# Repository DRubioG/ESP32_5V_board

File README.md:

# ESP32_5V
 This board updates the voltage of an ESP32

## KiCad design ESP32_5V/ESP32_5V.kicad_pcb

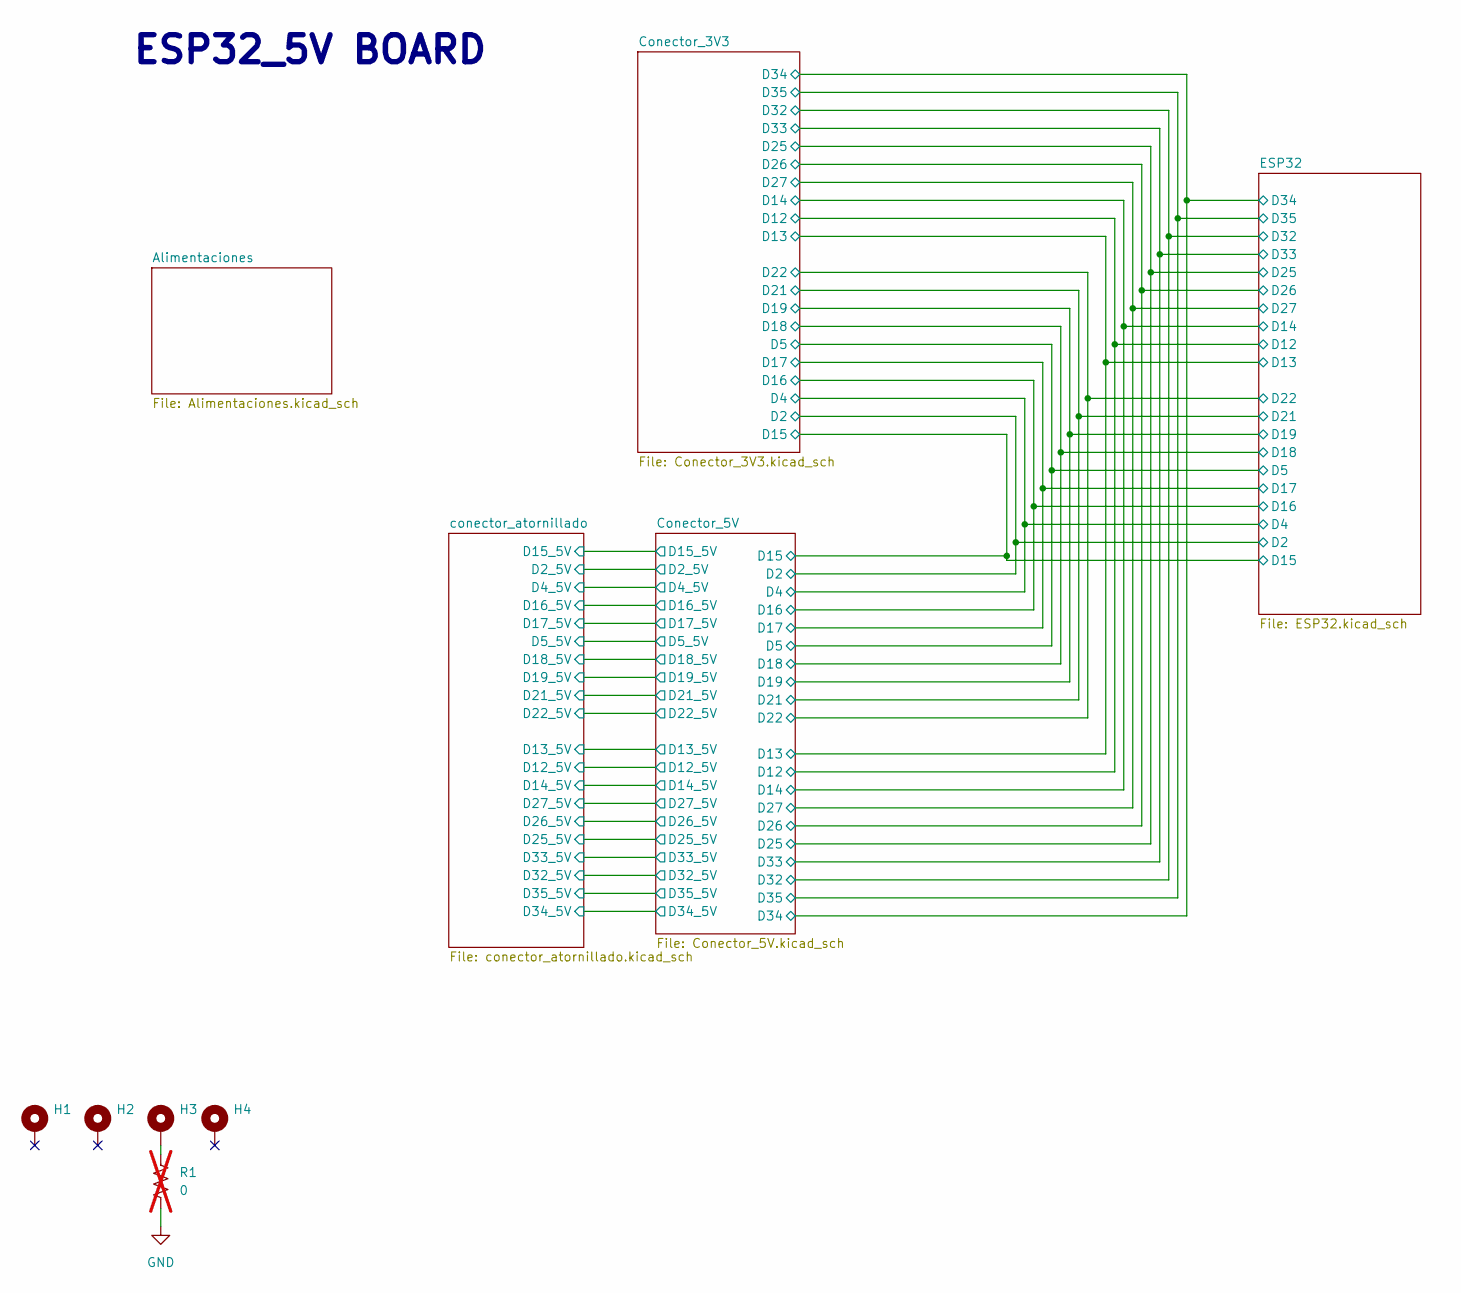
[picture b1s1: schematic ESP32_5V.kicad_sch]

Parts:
H1, H2, H3, H4: MountingHole_Pad; MountingHole_3.2mm_M3_Pad_Via
R1: 0; R_0805_2012Metric_Pad1.20x1.40mm_HandSolder; not fitted

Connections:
GND: R1.2; also elsewhere on the board
unnamed: H3.1 (1_1), R1.1

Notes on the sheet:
ESP32_5V BOARD

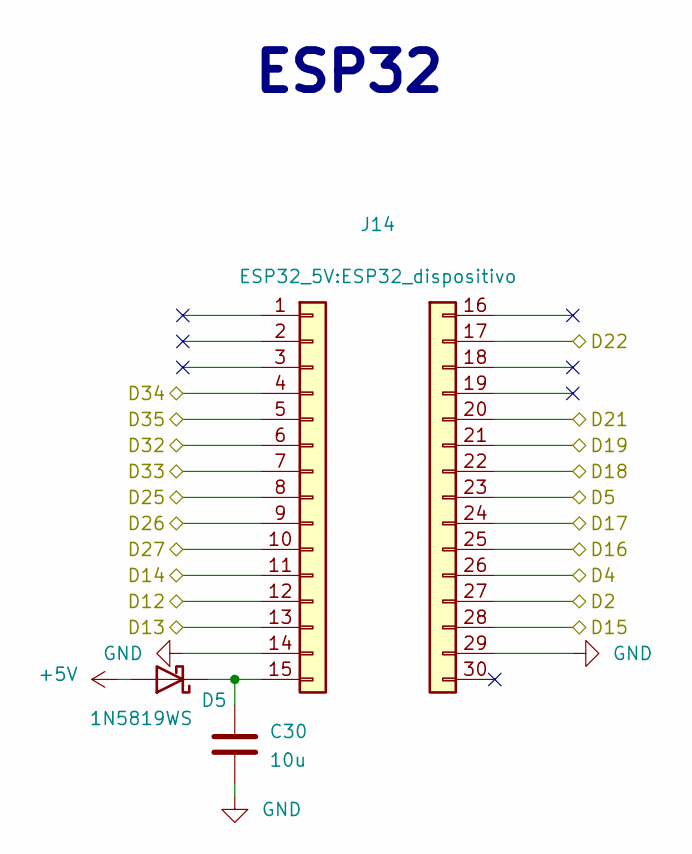
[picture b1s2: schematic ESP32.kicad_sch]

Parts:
C30: 10u; C_1206_3216Metric
D5: 1N5819WS; D_SOD-323
J14: ESP32_dispositivo

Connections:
+5V: D5.2 (A); also elsewhere on the board
/Conector_3V3/D2: J14.27; also elsewhere on the board
/Conector_3V3/D4: J14.26; also elsewhere on the board
/Conector_3V3/D5: J14.23; also elsewhere on the board
/Conector_3V3/D12: J14.12; also elsewhere on the board
/Conector_3V3/D13: J14.13; also elsewhere on the board
/Conector_3V3/D14: J14.11; also elsewhere on the board
/Conector_3V3/D15: J14.28; also elsewhere on the board
/Conector_3V3/D16: J14.25; also elsewhere on the board
/Conector_3V3/D17: J14.24; also elsewhere on the board
/Conector_3V3/D18: J14.22; also elsewhere on the board
/Conector_3V3/D19: J14.21; also elsewhere on the board
/Conector_3V3/D21: J14.20; also elsewhere on the board
/Conector_3V3/D22: J14.17; also elsewhere on the board
/Conector_3V3/D25: J14.8; also elsewhere on the board
/Conector_3V3/D26: J14.9; also elsewhere on the board
/Conector_3V3/D27: J14.10; also elsewhere on the board
/Conector_3V3/D32: J14.6; also elsewhere on the board
/Conector_3V3/D33: J14.7; also elsewhere on the board
/Conector_3V3/D34: J14.4; also elsewhere on the board
/Conector_3V3/D35: J14.5; also elsewhere on the board
GND: C30.2, J14.14, J14.29; also elsewhere on the board
unnamed: C30.1, D5.1 (K), J14.15

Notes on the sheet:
ESP32

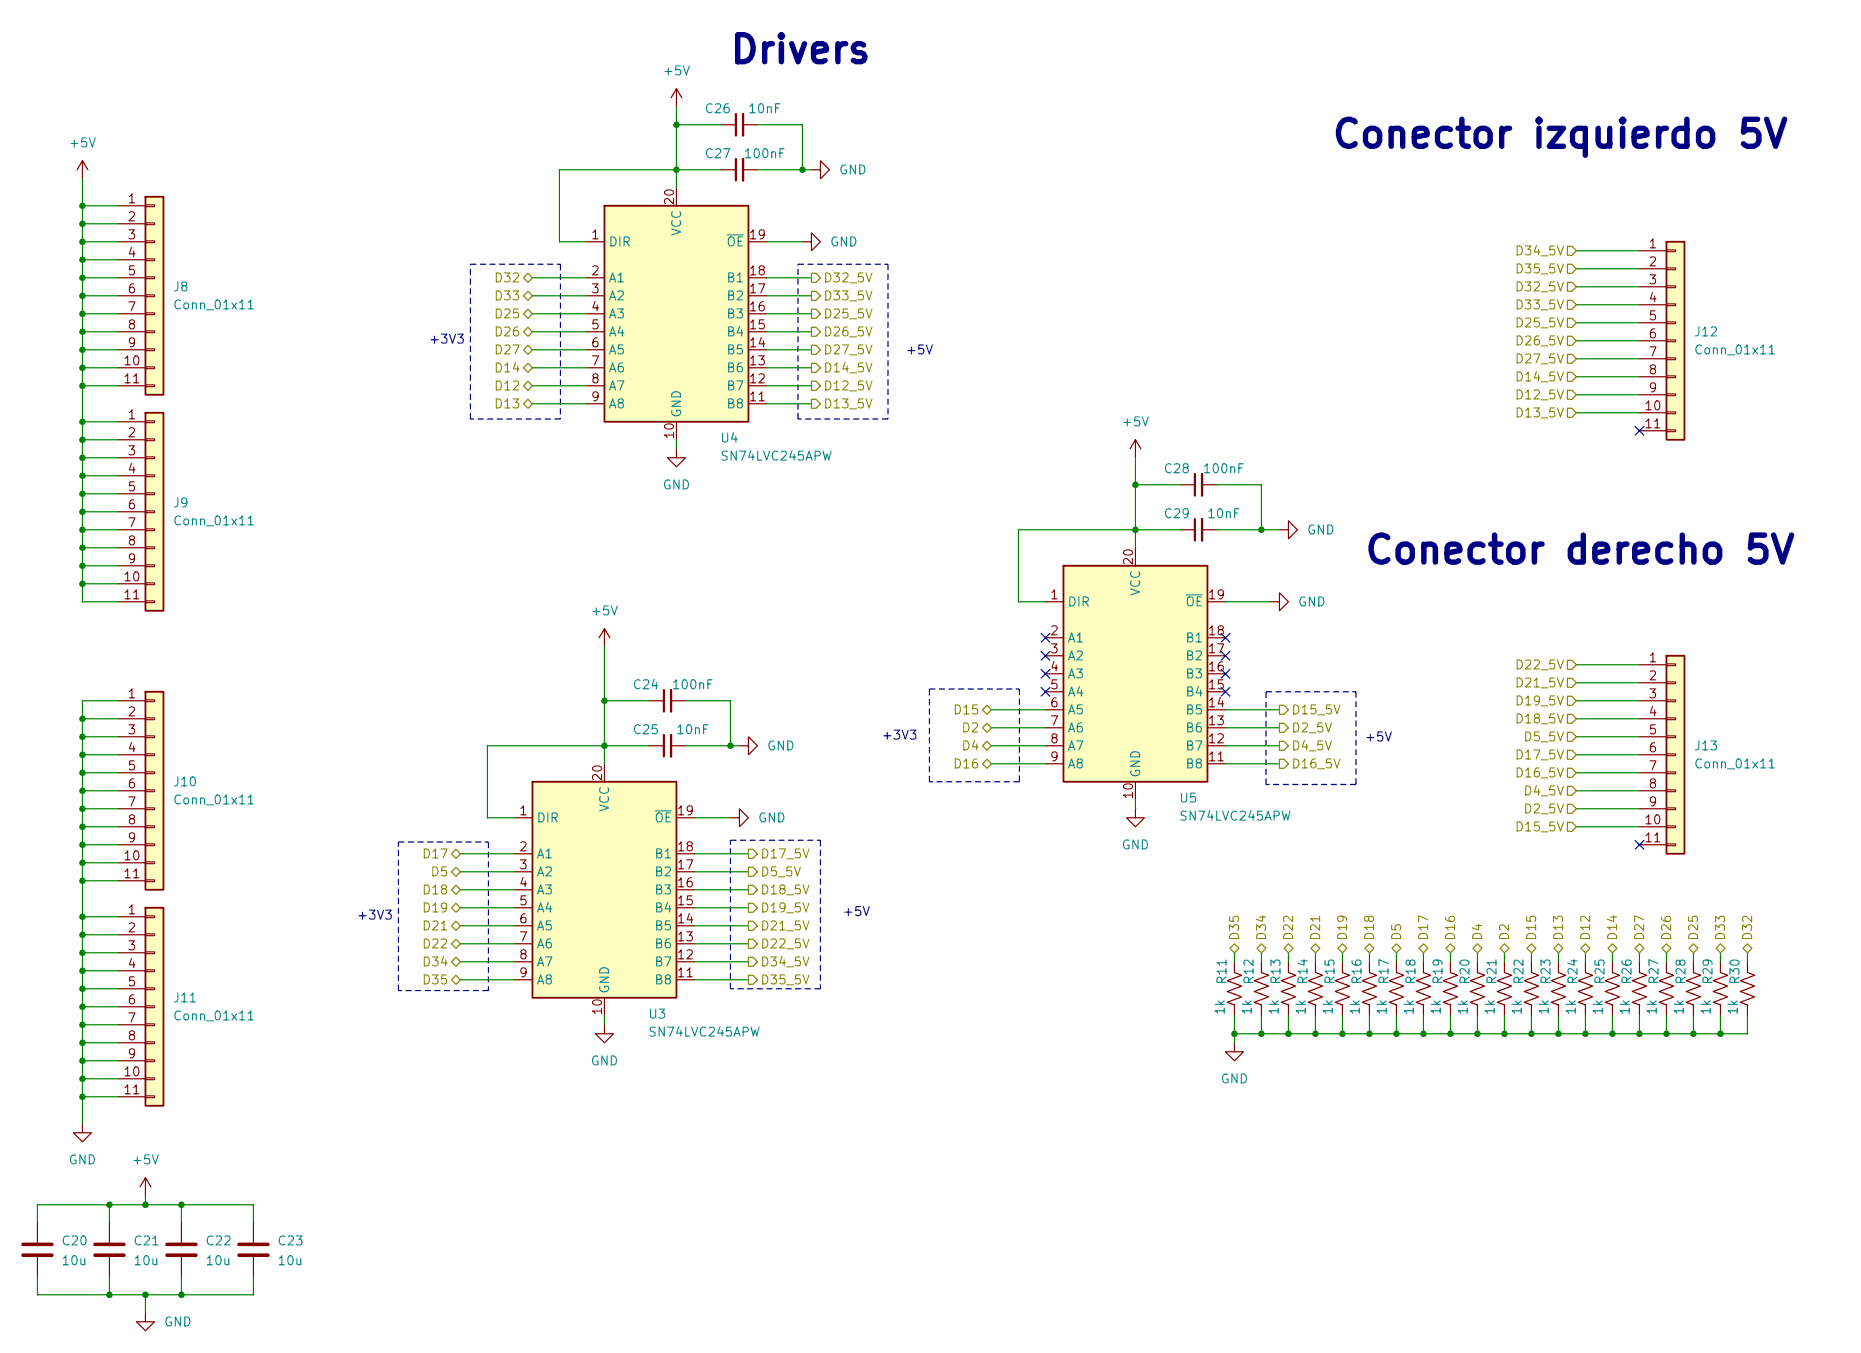
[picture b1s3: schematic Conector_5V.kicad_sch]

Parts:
C20, C21, C22, C23: 10u; C_1206_3216Metric
C24, C27, C28: 100nF; C_0805_2012Metric_Pad1.18x1.45mm_HandSolder
C25, C26, C29: 10nF; C_0805_2012Metric_Pad1.18x1.45mm_HandSolder
J8, J9, J10, J11, J12, J13: Conn_01x11; PinHeader_1x11_P2.54mm_Vertical
R11, R12, R13, R14, R15, R16, R17, R18, R19, R20, R21, R22, R23, R24, R25, R26, R27, R28, R29, R30: 1k; R_0805_2012Metric_Pad1.20x1.40mm_HandSolder
U3, U4, U5: SN74LVC245APW; TSSOP-20_4.4x6.5mm_P0.65mm

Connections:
+5V: C20.1, C21.1, C22.1, C23.1, C24.1, C25.1, C26.1, C27.1, C28.1, C29.1, J8.1, J8.2, J8.3, J8.4, J8.5, J8.6, J8.7, J8.8, J8.9, J8.10, J8.11, J9.1, J9.2, J9.3, J9.4, J9.5, J9.6, J9.7, J9.8, J9.9, J9.10, J9.11, U3.1 (DIR), U3.20 (VCC), U4.1 (DIR), U4.20 (VCC), U5.1 (DIR), U5.20 (VCC); also elsewhere on the board
/Conector_3V3/D2: R21.1, U5.7 (A6); also elsewhere on the board
/Conector_3V3/D4: R20.1, U5.8 (A7); also elsewhere on the board
/Conector_3V3/D5: R17.1, U3.3 (A2); also elsewhere on the board
/Conector_3V3/D12: R24.1, U4.8 (A7); also elsewhere on the board
/Conector_3V3/D13: R23.1, U4.9 (A8); also elsewhere on the board
/Conector_3V3/D14: R25.1, U4.7 (A6); also elsewhere on the board
/Conector_3V3/D15: R22.1, U5.6 (A5); also elsewhere on the board
/Conector_3V3/D16: R19.1, U5.9 (A8); also elsewhere on the board
/Conector_3V3/D17: R18.1, U3.2 (A1); also elsewhere on the board
/Conector_3V3/D18: R16.1, U3.4 (A3); also elsewhere on the board
/Conector_3V3/D19: R15.1, U3.5 (A4); also elsewhere on the board
/Conector_3V3/D21: R14.1, U3.6 (A5); also elsewhere on the board
/Conector_3V3/D22: R13.1, U3.7 (A6); also elsewhere on the board
/Conector_3V3/D25: R28.1, U4.4 (A3); also elsewhere on the board
/Conector_3V3/D26: R27.1, U4.5 (A4); also elsewhere on the board
/Conector_3V3/D27: R26.1, U4.6 (A5); also elsewhere on the board
/Conector_3V3/D32: R30.1, U4.2 (A1); also elsewhere on the board
/Conector_3V3/D33: R29.1, U4.3 (A2); also elsewhere on the board
/Conector_3V3/D34: R12.1, U3.8 (A7); also elsewhere on the board
/Conector_3V3/D35: R11.1, U3.9 (A8); also elsewhere on the board
/Conector_5V/D2_5V: J13.9, U5.13 (B6); also elsewhere on the board
/Conector_5V/D4_5V: J13.8, U5.12 (B7); also elsewhere on the board
/Conector_5V/D5_5V: J13.5, U3.17 (B2); also elsewhere on the board
/Conector_5V/D12_5V: J12.9, U4.12 (B7); also elsewhere on the board
/Conector_5V/D13_5V: J12.10, U4.11 (B8); also elsewhere on the board
/Conector_5V/D14_5V: J12.8, U4.13 (B6); also elsewhere on the board
/Conector_5V/D15_5V: J13.10, U5.14 (B5); also elsewhere on the board
/Conector_5V/D16_5V: J13.7, U5.11 (B8); also elsewhere on the board
/Conector_5V/D17_5V: J13.6, U3.18 (B1); also elsewhere on the board
/Conector_5V/D18_5V: J13.4, U3.16 (B3); also elsewhere on the board
/Conector_5V/D19_5V: J13.3, U3.15 (B4); also elsewhere on the board
/Conector_5V/D21_5V: J13.2, U3.14 (B5); also elsewhere on the board
/Conector_5V/D22_5V: J13.1, U3.13 (B6); also elsewhere on the board
/Conector_5V/D25_5V: J12.5, U4.16 (B3); also elsewhere on the board
/Conector_5V/D26_5V: J12.6, U4.15 (B4); also elsewhere on the board
/Conector_5V/D27_5V: J12.7, U4.14 (B5); also elsewhere on the board
/Conector_5V/D32_5V: J12.3, U4.18 (B1); also elsewhere on the board
/Conector_5V/D33_5V: J12.4, U4.17 (B2); also elsewhere on the board
/Conector_5V/D34_5V: J12.1, U3.12 (B7); also elsewhere on the board
/Conector_5V/D35_5V: J12.2, U3.11 (B8); also elsewhere on the board
GND: C20.2, C21.2, C22.2, C23.2, C24.2, C25.2, C26.2, C27.2, C28.2, C29.2, J10.1, J10.2, J10.3, J10.4, J10.5, J10.6, J10.7, J10.8, J10.9, J10.10, J10.11, J11.1, J11.2, J11.3, J11.4, J11.5, J11.6, J11.7, J11.8, J11.9, J11.10, J11.11, R11.2, R12.2, R13.2, R14.2, R15.2, R16.2, R17.2, R18.2, R19.2, R20.2, R21.2, R22.2, R23.2, R24.2, R25.2, R26.2, R27.2, R28.2, R29.2, R30.2, U3.10 (GND), U3.19 (~OE), U4.10 (GND), U4.19 (~OE), U5.10 (GND), U5.19 (~OE); also elsewhere on the board

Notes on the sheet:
Conector izquierdo 5V
+5V
+3V3
Conector derecho 5V
Drivers

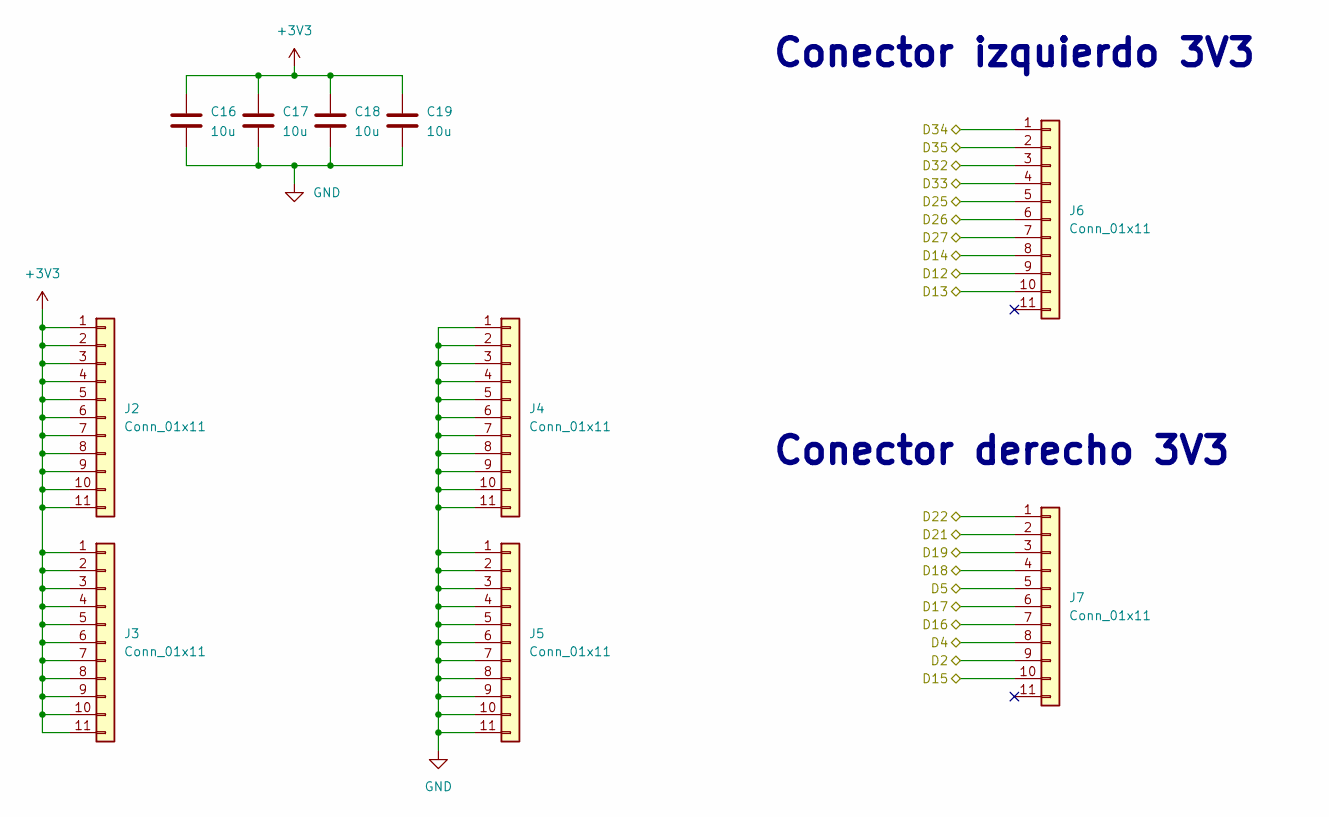
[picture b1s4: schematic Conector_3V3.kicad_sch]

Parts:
C16, C17, C18, C19: 10u; C_1206_3216Metric
J2, J3, J4, J5, J6, J7: Conn_01x11; PinHeader_1x11_P2.54mm_Vertical

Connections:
+3V3: C16.1, C17.1, C18.1, C19.1, J2.1, J2.2, J2.3, J2.4, J2.5, J2.6, J2.7, J2.8, J2.9, J2.10, J2.11, J3.1, J3.2, J3.3, J3.4, J3.5, J3.6, J3.7, J3.8, J3.9, J3.10, J3.11; also elsewhere on the board
/Conector_3V3/D2: J7.9; also elsewhere on the board
/Conector_3V3/D4: J7.8; also elsewhere on the board
/Conector_3V3/D5: J7.5; also elsewhere on the board
/Conector_3V3/D12: J6.9; also elsewhere on the board
/Conector_3V3/D13: J6.10; also elsewhere on the board
/Conector_3V3/D14: J6.8; also elsewhere on the board
/Conector_3V3/D15: J7.10; also elsewhere on the board
/Conector_3V3/D16: J7.7; also elsewhere on the board
/Conector_3V3/D17: J7.6; also elsewhere on the board
/Conector_3V3/D18: J7.4; also elsewhere on the board
/Conector_3V3/D19: J7.3; also elsewhere on the board
/Conector_3V3/D21: J7.2; also elsewhere on the board
/Conector_3V3/D22: J7.1; also elsewhere on the board
/Conector_3V3/D25: J6.5; also elsewhere on the board
/Conector_3V3/D26: J6.6; also elsewhere on the board
/Conector_3V3/D27: J6.7; also elsewhere on the board
/Conector_3V3/D32: J6.3; also elsewhere on the board
/Conector_3V3/D33: J6.4; also elsewhere on the board
/Conector_3V3/D34: J6.1; also elsewhere on the board
/Conector_3V3/D35: J6.2; also elsewhere on the board
GND: C16.2, C17.2, C18.2, C19.2, J4.1, J4.2, J4.3, J4.4, J4.5, J4.6, J4.7, J4.8, J4.9, J4.10, J4.11, J5.1, J5.2, J5.3, J5.4, J5.5, J5.6, J5.7, J5.8, J5.9, J5.10, J5.11; also elsewhere on the board

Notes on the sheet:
Conector derecho 3V3
Conector izquierdo 3V3

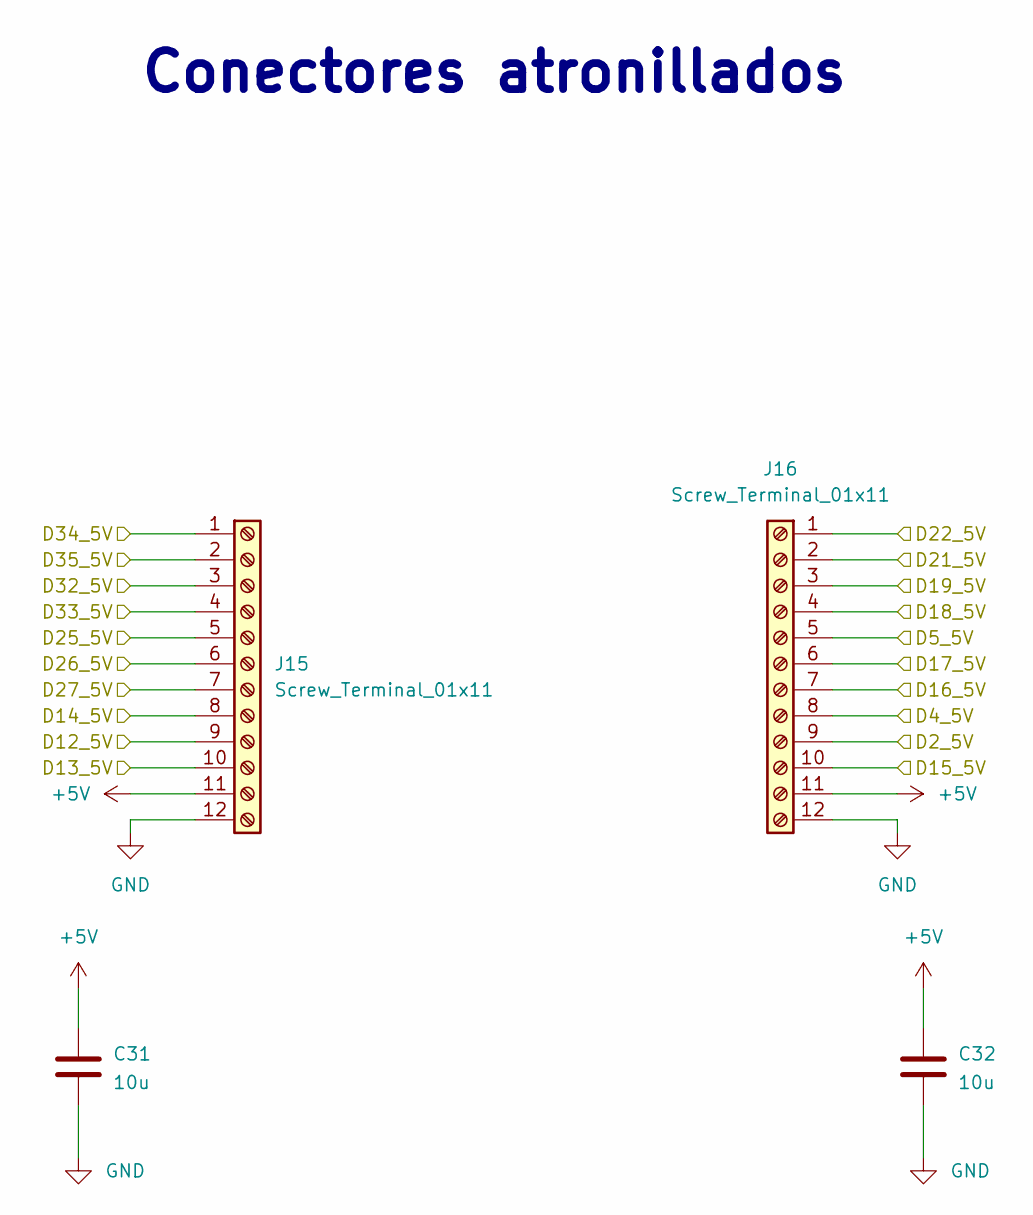
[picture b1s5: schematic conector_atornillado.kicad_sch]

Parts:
C31, C32: 10u; C_1206_3216Metric
J15, J16: Screw_Terminal_01x11; PinHeader_1x12_P2.54mm_Vertical

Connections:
+5V: C31.1, C32.1, J15.11, J16.11; also elsewhere on the board
/Conector_5V/D2_5V: J16.9; also elsewhere on the board
/Conector_5V/D4_5V: J16.8; also elsewhere on the board
/Conector_5V/D5_5V: J16.5; also elsewhere on the board
/Conector_5V/D12_5V: J15.9; also elsewhere on the board
/Conector_5V/D13_5V: J15.10; also elsewhere on the board
/Conector_5V/D14_5V: J15.8; also elsewhere on the board
/Conector_5V/D15_5V: J16.10; also elsewhere on the board
/Conector_5V/D16_5V: J16.7; also elsewhere on the board
/Conector_5V/D17_5V: J16.6; also elsewhere on the board
/Conector_5V/D18_5V: J16.4; also elsewhere on the board
/Conector_5V/D19_5V: J16.3; also elsewhere on the board
/Conector_5V/D21_5V: J16.2; also elsewhere on the board
/Conector_5V/D22_5V: J16.1; also elsewhere on the board
/Conector_5V/D25_5V: J15.5; also elsewhere on the board
/Conector_5V/D26_5V: J15.6; also elsewhere on the board
/Conector_5V/D27_5V: J15.7; also elsewhere on the board
/Conector_5V/D32_5V: J15.3; also elsewhere on the board
/Conector_5V/D33_5V: J15.4; also elsewhere on the board
/Conector_5V/D34_5V: J15.1; also elsewhere on the board
/Conector_5V/D35_5V: J15.2; also elsewhere on the board
GND: C31.2, C32.2, J15.12, J16.12; also elsewhere on the board

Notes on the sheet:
Conectores atronillados

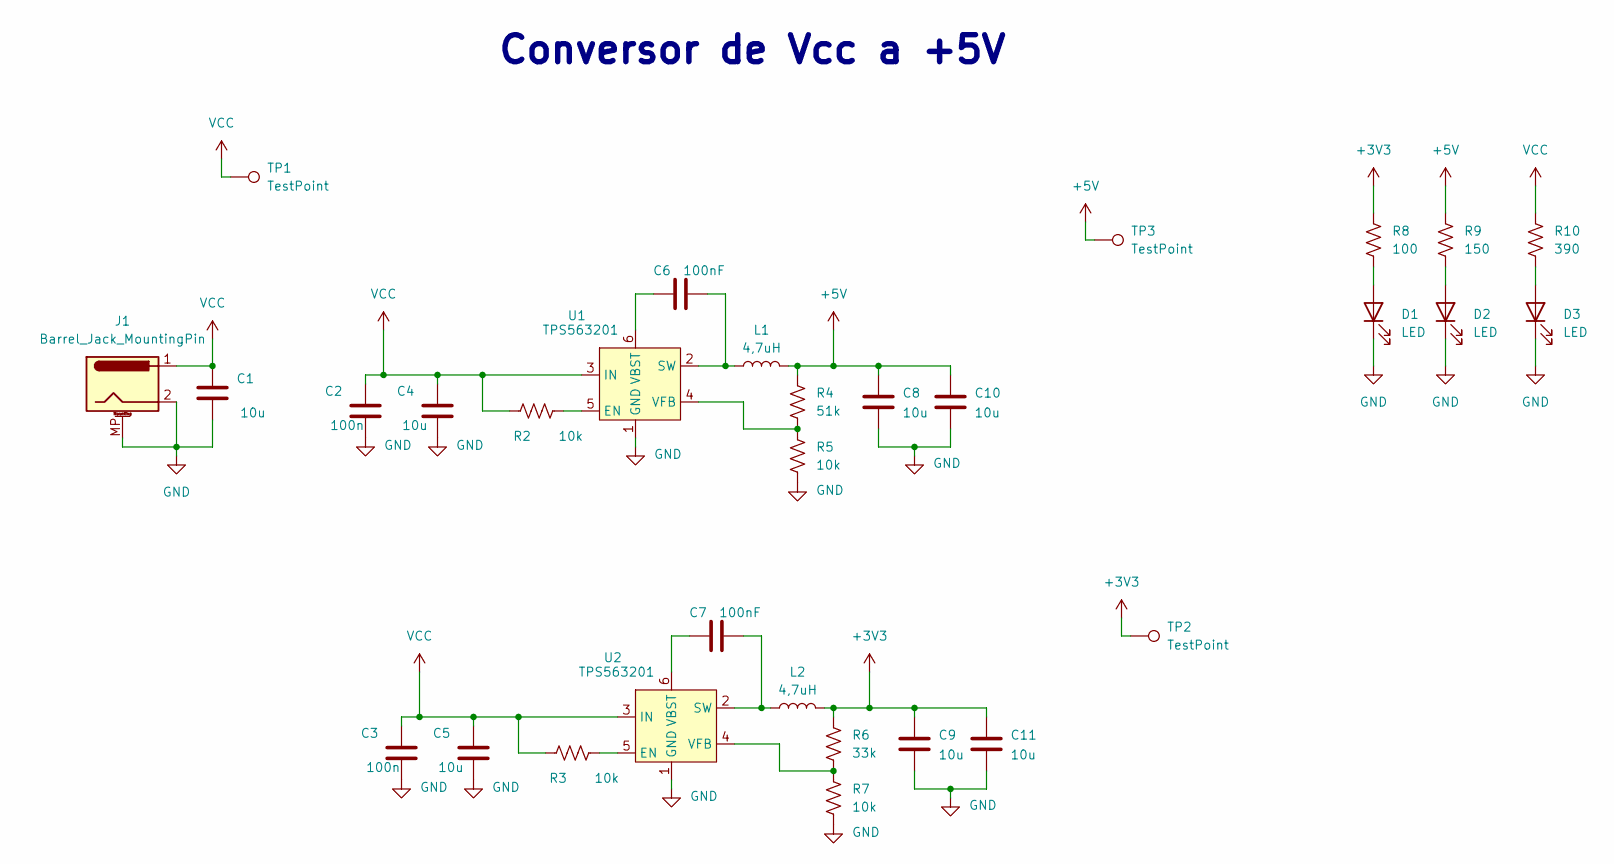
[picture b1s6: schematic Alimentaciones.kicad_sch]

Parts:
C1, C4, C5: 10u; C_1210_3225Metric
C2, C3: 100n; C_0805_2012Metric_Pad1.18x1.45mm_HandSolder
C6, C7: 100nF; C_0805_2012Metric_Pad1.18x1.45mm_HandSolder
C8, C9, C10, C11: 10u; C_1206_3216Metric
D1, D2, D3: LED; LED_0805_2012Metric_Pad1.15x1.40mm_HandSolder
J1: Barrel_Jack_MountingPin; BarrelJack_GCT_DCJ200-10-A_Horizontal
L1, L2: 4,7uH; L_6.3x6.3_H3
R2, R3, R5, R7: 10k; R_0805_2012Metric_Pad1.20x1.40mm_HandSolder
R4: 51k; R_0805_2012Metric_Pad1.20x1.40mm_HandSolder
R6: 33k; R_0805_2012Metric_Pad1.20x1.40mm_HandSolder
R8: 100; R_0805_2012Metric_Pad1.20x1.40mm_HandSolder
R9: 150; R_0805_2012Metric_Pad1.20x1.40mm_HandSolder
R10: 390; R_0805_2012Metric_Pad1.20x1.40mm_HandSolder
TP1, TP2, TP3: TestPoint; TestPoint_Pad_D2.0mm
U1, U2: TPS563201; SOT-23-6

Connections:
+3V3: C9.1, C11.1, L2.2, R6.1, R8.1, TP2.1 (1_1); also elsewhere on the board
+5V: C8.1, C10.1, L1.2, R4.1, R9.1, TP3.1 (1_1); also elsewhere on the board
GND: C1.2, C2.2, C3.2, C4.2, C5.2, C8.2, C9.2, C10.2, C11.2, D1.1 (K), D2.1 (K), D3.1 (K), J1.2, J1.MP (MountPin), R5.2, R7.2, U1.1 (GND), U2.1 (GND); also elsewhere on the board
unnamed: D1.2 (A), R8.2
unnamed: D2.2 (A), R9.2
unnamed: D3.2 (A), R10.2
unnamed: R2.1, U1.5 (EN)
unnamed: C6.2, L1.1, U1.2 (SW)
unnamed: C6.1, U1.6 (VBST)
unnamed: R4.2, R5.1, U1.4 (VFB)
unnamed: R3.1, U2.5 (EN)
unnamed: C7.2, L2.1, U2.2 (SW)
unnamed: C7.1, U2.6 (VBST)
unnamed: R6.2, R7.1, U2.4 (VFB)
VCC: C1.1, C2.1, C3.1, C4.1, C5.1, J1.1, R2.2, R3.2, R10.1, TP1.1 (1_1), U1.3 (IN), U2.3 (IN)

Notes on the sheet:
Conversor de Vcc a +5V

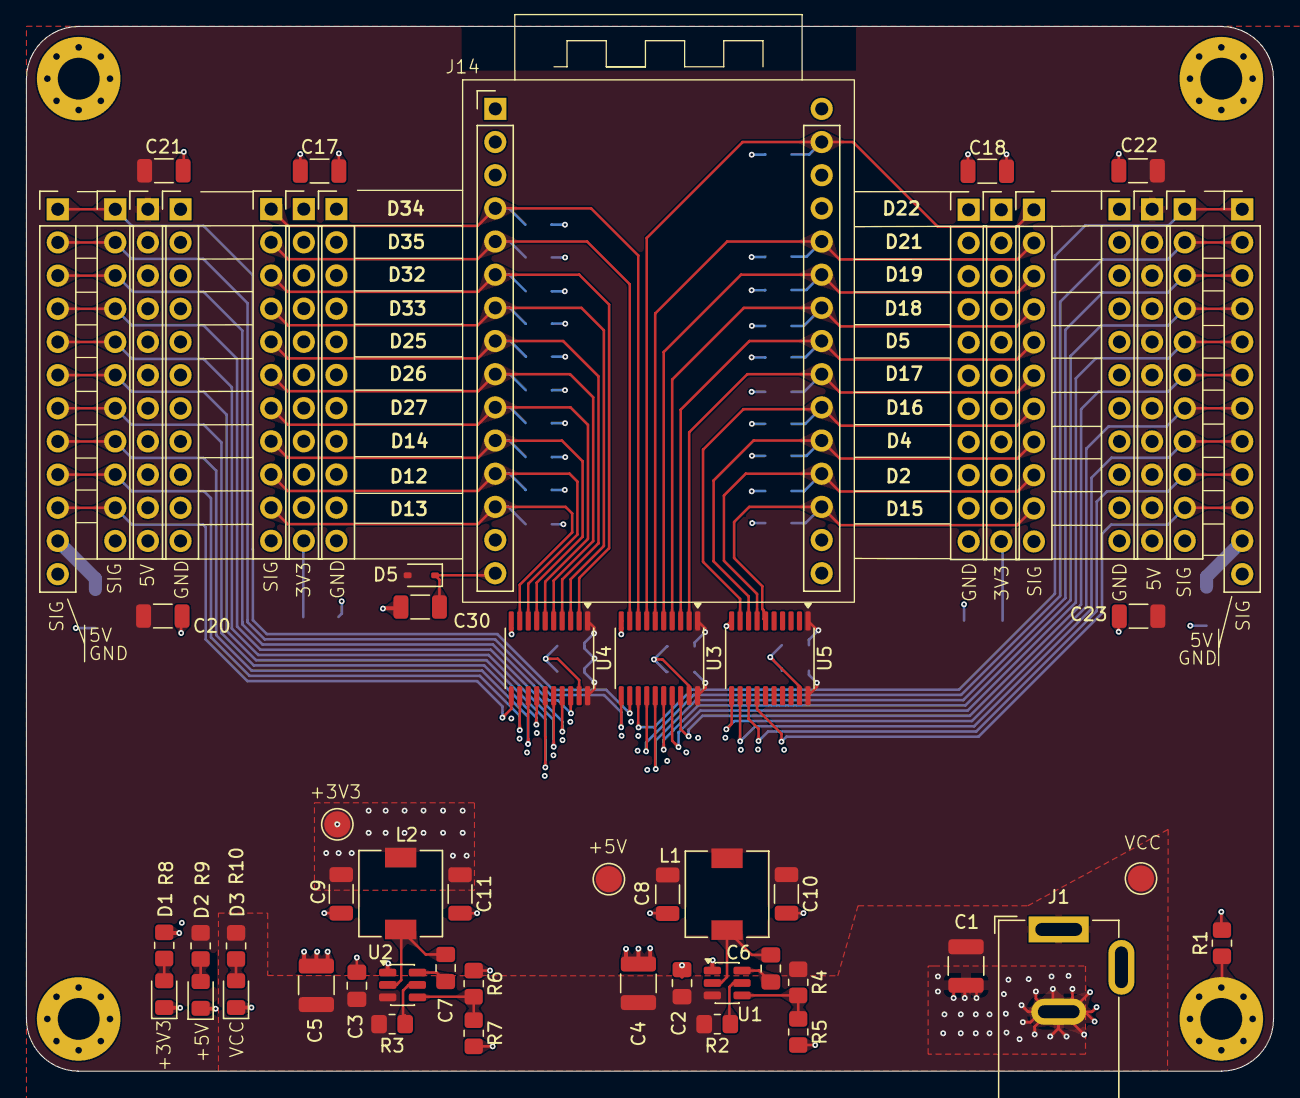
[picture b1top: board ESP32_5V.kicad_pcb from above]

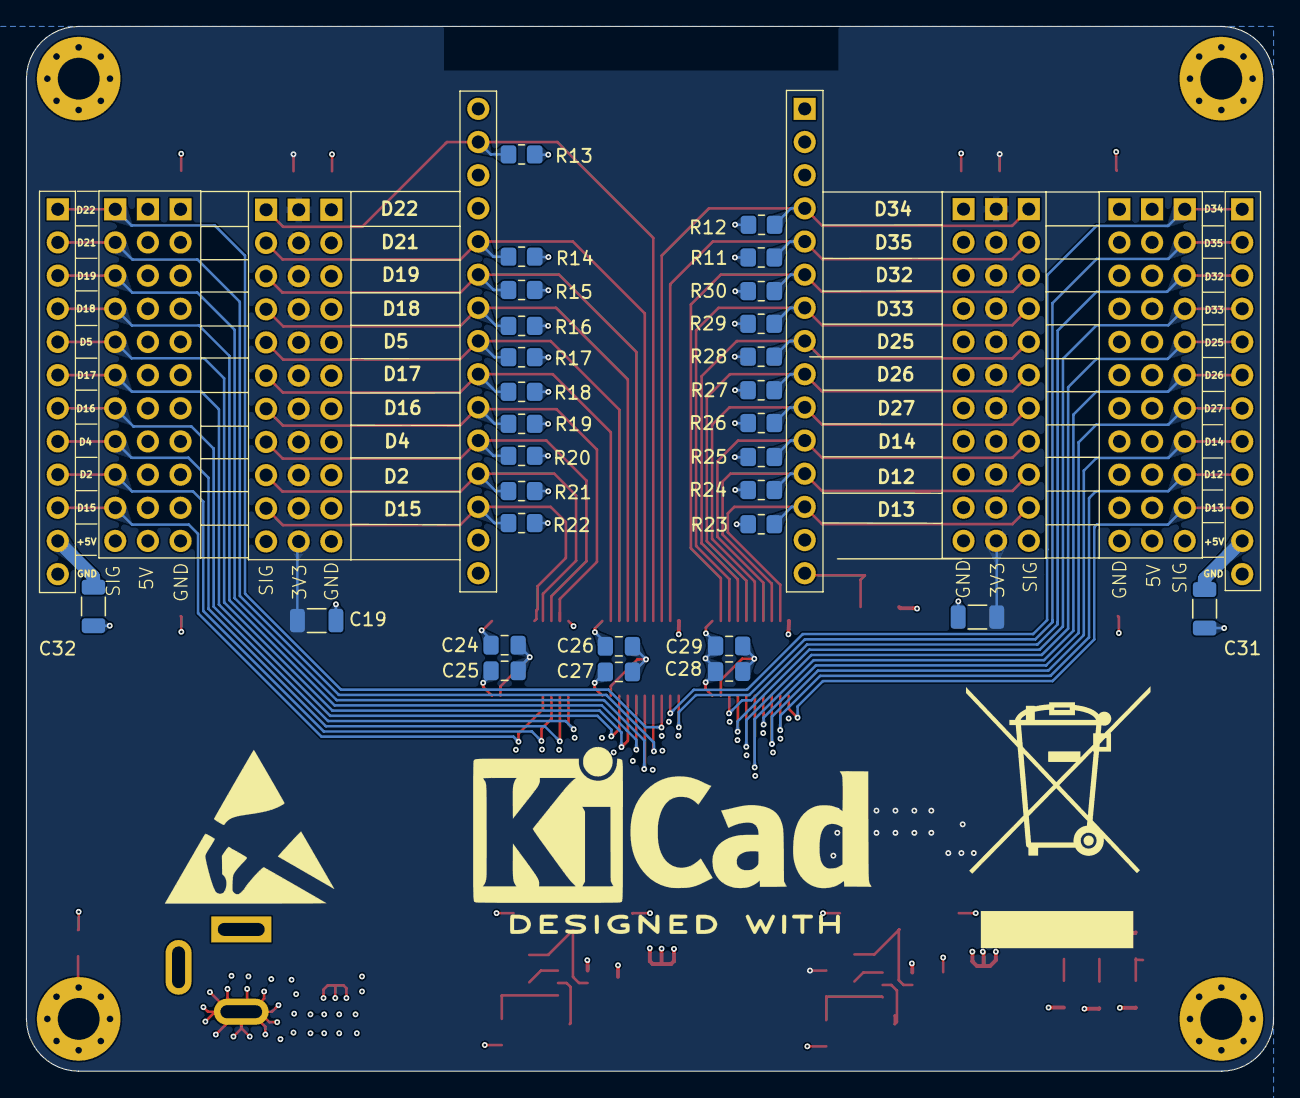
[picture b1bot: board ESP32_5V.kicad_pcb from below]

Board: 4 copper layers, 95.5 x 80.0 mm, 92 parts (30 on the bottom side), 57 nets.
